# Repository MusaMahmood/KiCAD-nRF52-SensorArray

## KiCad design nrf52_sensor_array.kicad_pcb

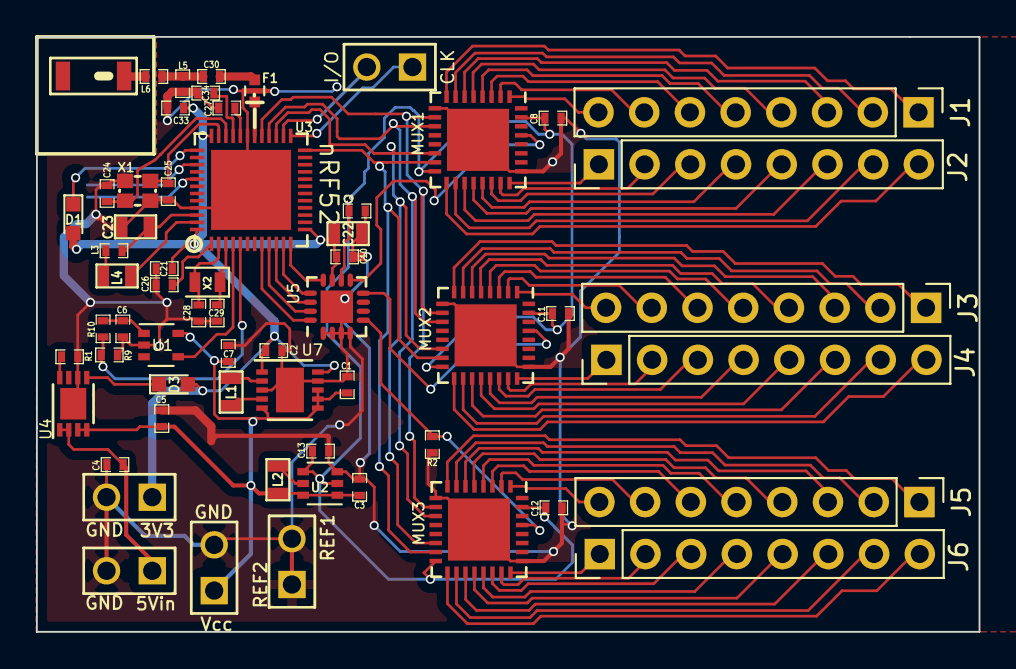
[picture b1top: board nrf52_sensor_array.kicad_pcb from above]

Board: 2 copper layers, 52.4 x 33.1 mm, 61 parts (0 on the bottom side), 90 nets.

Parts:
A1: CHIP-ANT; JTI-2450AT18A100-CHIP-ANT
C1, C2, C3, C6, C7, C13: 10uF; SM0402
C4, C5, C8, C11, C12: 4.7uF; SM0402
C9, C10: 0.1uF; SM0402
C21: 4.7µF; SM0402
C22: 100nF; SM0603
C23: 1.0µF; SM0603
C24, C25, C28, C29: 12pF; SM0402
C26, C33: 100nF; SM0402
C27: N.C.; SM0402
C30: 1.0pF; SM0402
C34: 100pF; SM0402
D1, D3: LED; LED_0603
F1: 2450FM07A0029; R_0402
J1, J2, J3, J4, J5, J6: CONN_01X08; Pin_Header_Straight_1x08_Pitch2.54mm
L1: 2.2µH; SM0603
L2: 4.7µH; SM0603
L3: 15nH; SM0402
L4: 10uH; SM0603
L5: 2.7nH; SM0402
L6: 3.9nH; SM0402
MUX1, MUX2, MUX3: ADG1606; QFN-32-1EP_5x5mm_Pitch0.5mm
P1, P2, P3, P4, P5: CONN_2; PIN_ARRAY_2X1
R1, R2: 2k; SM0402
R9, R10: 1M; SM0402
U1: TPS2294x; SOT-353_SC-70-5
U2: TPS61222; SOT-363_SC-70-6
U3: NRF528XX-QFAA; UQFN-48-1EP_6x6mm_Pitch0.4mm
U4: MCP73831; DFN-8-1EP_3x2mm_Pitch0.5mm
U5: ADS1220; QFN-16-1EP_3x3mm_Pitch0.5mm
U7: TPS63001; DFN-10-1EP_3x3mm_Pitch0.5mm
X1: Crystal_GND24; CRYSTAL-SMD-2.0MMx1.6MM
X2: 32.768 kHz; Crystal_SMD_2012-2pin_2.0x1.2mm

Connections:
5V_in_charge: C4.2, P1.1, U4.1, U4.2
/AIN_BAT_DIV_VOLTAGE: R9.2, R10.1, U3.5
/DEC1: C26.1, U3.1
/DEC2: C27.1, U3.32
/DEC3: C34.1, U3.33
/DIN: U3.10, U5.14
/DOUT: U3.11, U5.13
/LED1: D1.1, U3.37
/LOAD_SW_CTRL: U1.4, U3.4
/RF: C30.1, F1.4
/SPI_SCLK: U3.9, U5.15
/SPI_~CS: U3.8, U5.16
/SWDCLK: P2.1, U3.25
/SWDIO: P2.2, U3.26
/Vout: C6.1, R10.2, U1.1
/ctr_m1_a0: MUX1.15, MUX2.15, MUX3.15, U3.24
/ctr_m1_a1: MUX1.14, MUX2.14, MUX3.14, U3.27
/ctr_m1_a2: MUX1.11, MUX2.11, MUX3.11, U3.28
/ctr_m1_a3: MUX1.10, MUX2.10, MUX3.10, U3.29
/m1_D_out: MUX1.29, U5.9
/m2_D_out: MUX2.29, U5.8
/m3_D_out: MUX3.29, R2.2, U5.5
/~DRDY: U3.12, U5.12
AVDD: C8.1, C9.1, C11.1, C12.1, C13.1, MUX1.16, MUX1.31, MUX2.16, MUX2.31, MUX3.16, MUX3.31, U2.2, U2.4, U5.10
AVSS: C1.1, C2.2, C3.2, C4.1, C5.1, C6.2, C7.2, C8.2, C9.2, C10.1, C11.2, C12.2, C13.2, C21.1, C22.2, C23.2, C24.1, C25.1, C26.2, C27.2, C28.2, C29.2, C33.1, C34.2, F1.1, F1.3, L5.2, MUX1.9, MUX1.25, MUX1.33, MUX2.9, MUX2.25, MUX2.33, MUX3.9, MUX3.25, MUX3.33, P1.2, P3.2, P4.1, P4.2, P5.2, R1.1, R2.1, R9.1, U1.2, U2.3, U3.31, U3.45, U3.49, U4.6, U4.9, U5.1, U5.2, U5.3, U5.4, U5.17, U7.3, U7.9, U7.11, X1.2, X1.4
DVDD: C2.1, C10.2, C21.2, C22.1, C33.2, D1.2, D3.2, P5.1, U3.13, U3.36, U3.48, U5.11, U7.1, U7.10
unnamed: A1.1, L6.2
unnamed: C23.1, L3.2, U3.46
unnamed: C24.2, U3.34, X1.1
unnamed: C25.2, U3.35, X1.3
unnamed: C28.1, U3.2, X2.2
unnamed: C29.1, U3.3, X2.1
unnamed: C30.2, L5.1, L6.1
unnamed: D3.1, U4.5
unnamed: F1.2, U3.30
unnamed: J1.1, MUX1.8
unnamed: J1.2, MUX1.7
unnamed: J1.3, MUX1.6
unnamed: J1.4, MUX1.5
unnamed: J1.5, MUX1.4
unnamed: J1.6, MUX1.3
unnamed: J1.7, MUX1.2
unnamed: J1.8, MUX1.1
unnamed: J2.1, MUX1.24
unnamed: J2.2, MUX1.23
unnamed: J2.3, MUX1.22
unnamed: J2.4, MUX1.21
unnamed: J2.5, MUX1.20
unnamed: J2.6, MUX1.19
unnamed: J2.7, MUX1.18
unnamed: J2.8, MUX1.17
unnamed: J3.1, MUX2.8
unnamed: J3.2, MUX2.7
unnamed: J3.3, MUX2.6
unnamed: J3.4, MUX2.5
unnamed: J3.5, MUX2.4
unnamed: J3.6, MUX2.3
unnamed: J3.7, MUX2.2
unnamed: J3.8, MUX2.1
unnamed: J4.1, MUX2.24
unnamed: J4.2, MUX2.23
unnamed: J4.3, MUX2.22
unnamed: J4.4, MUX2.21
unnamed: J4.5, MUX2.20
unnamed: J4.6, MUX2.19
unnamed: J4.7, MUX2.18
unnamed: J4.8, MUX2.17
unnamed: J5.1, MUX3.8
unnamed: J5.2, MUX3.7
unnamed: J5.3, MUX3.6
unnamed: J5.4, MUX3.5
unnamed: J5.5, MUX3.4
unnamed: J5.6, MUX3.3
unnamed: J5.7, MUX3.2
unnamed: J5.8, MUX3.1
unnamed: J6.1, MUX3.24
unnamed: J6.2, MUX3.23
unnamed: J6.3, MUX3.22
unnamed: J6.4, MUX3.21
unnamed: J6.5, MUX3.20
unnamed: J6.6, MUX3.19
unnamed: J6.7, MUX3.18
unnamed: J6.8, MUX3.17
unnamed: L1.1, U7.4
unnamed: L1.2, U7.2
unnamed: L2.1, U2.5
unnamed: L3.1, L4.2
unnamed: L4.1, U3.47
unnamed: R1.2, U4.8
VCC: C1.2, C3.1, C5.2, C7.1, L2.2, P3.1, U1.5, U2.1, U2.6, U4.3, U4.4, U7.5, U7.6, U7.7, U7.8

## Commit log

2018-06-05 Initial Commit.
2018-06-05 Remove extraneous stuff from schematic.
2018-06-05 Linked new library (under libs_common). Added battery recharging circuit to schematic.
2018-06-05 Added battery management (recharging, MCP73831) circuit to device, using 500 mA configuration.
2018-06-08 Updated schematic with all components. Plan is to replace multiplexers with ADG1606 (single supply), and get rid of -5V regulator.
2018-06-08 Removed old muxes and -5V reguator. Updated schematic and added ADG1606, and 2 rows of headers.
2018-06-08 Added ADC: ADS1220, added 2/3 Multiplexers (ADG1606)
2018-06-08 Completed PCB.
2018-06-08 Updated .gitignore, added pins for 2 reference electrodes (grounded)
2018-06-08 Added option to short Reference electrodes to ground (using pad N1).
2018-06-11 Added voltage divider, pins for 3v3 power supply.
2018-06-11 Updated PCB and gerber files.
2018-06-26 Placed corrected footprint.
2018-10-11 (work in progress), missing ground connection on PCB, no load sharing circuit.
